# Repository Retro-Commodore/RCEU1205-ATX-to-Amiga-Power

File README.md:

# RCEU1205
 ATX to Amiga Power adapter for A500/600/1200 Tower
 
Make note that the pcb has not been testet yet, and shouldn't be considered a release just yet. 

# BOM

w/everything (*)
1x 24 pin ATX connector
5x Pins salvaged from a DIN connector
2x 4pin SIL header
7x 2pin SIL header

bare minimum (*)
1x 24 pin ATX connector
5x Pins salvaged from a DIN connector
1x 2pin SIL header

# Putting it all together
The pins from the DIN connector is soldered into the square din holes.

# Description
J2 is the power connector for the ATX power supply.

There are 2x 4pins headers for 12v psu's  pin1 = gnd, pin2 = 12v, pin3 = sense, pin4 = control
The 2x 2pins headers to the right gains access to pin 3 and 4 accordingly to the 12v pin header, in case you want to control the 12v fans using an arduino or similar.

There are 2x 2pins headers for 5v
And there are 2x 2pins headers for 3.3v
You can use these for whatever you want.

(*) the extra pin headers are not needed, but can be an extra help if you want to i.e. control fans using an arduino and temperature sensor.

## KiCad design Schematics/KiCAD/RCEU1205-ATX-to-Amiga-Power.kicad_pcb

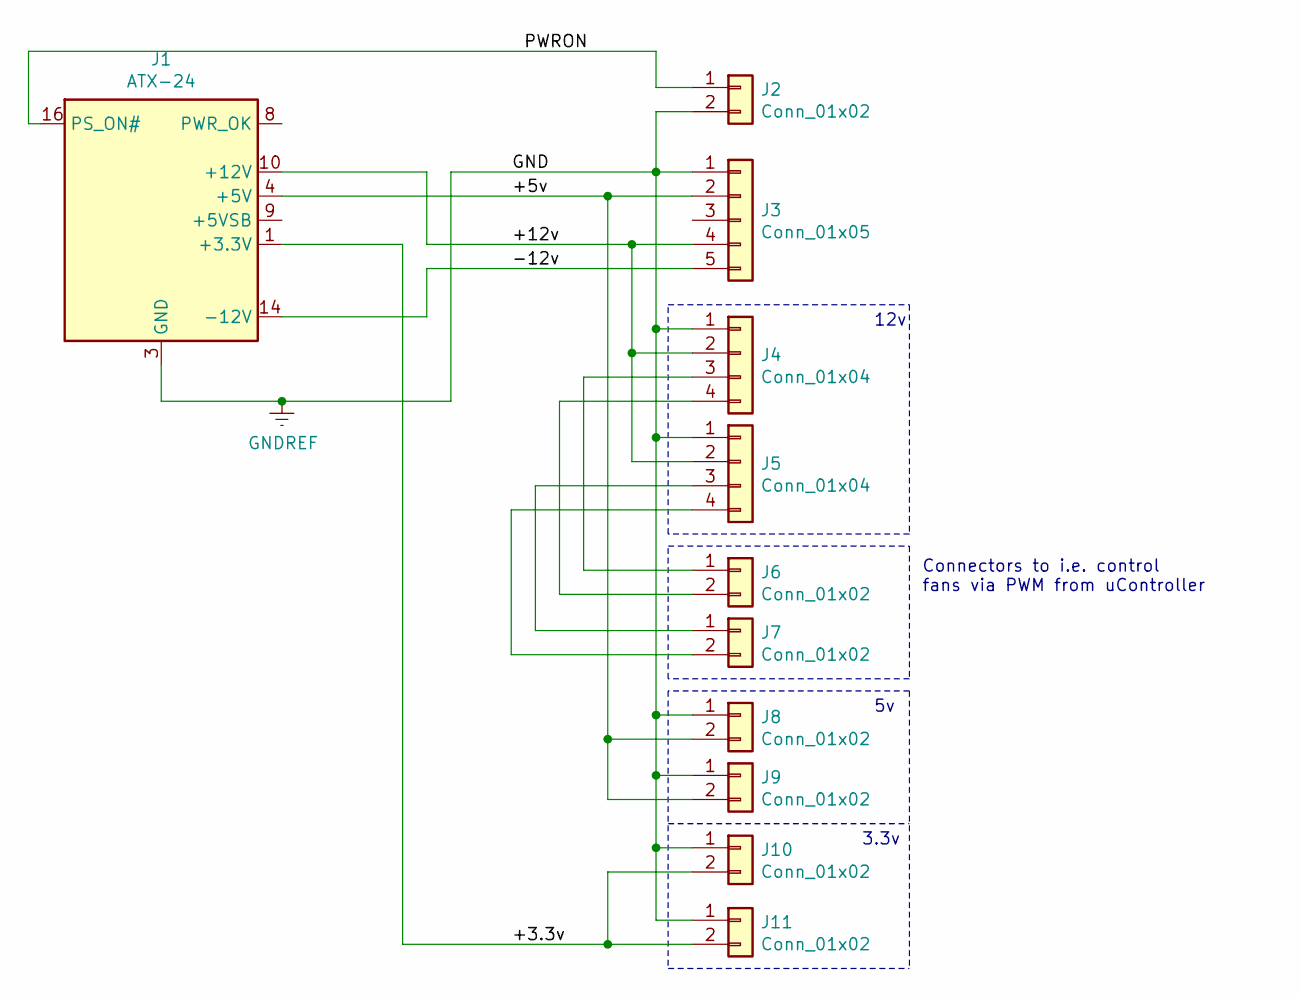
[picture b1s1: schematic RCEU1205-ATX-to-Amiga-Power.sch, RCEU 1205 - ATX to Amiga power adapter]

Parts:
J1: ATX-24; Molex_Mini-Fit_Jr_5566-24A_2x12_P4.20mm_Vertical
J2, J6, J7, J8, J9, J10, J11: Conn_01x02; PinHeader_1x02_P2.54mm_Vertical
J3: Conn_01x05; Connector_DIN_Square_5pin
J4, J5: Conn_01x04; PinHeader_1x04_P2.54mm_Vertical

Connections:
/+3.3v: J1.1 (+3.3V), J1.2 (+3.3V), J1.12 (+3.3V), J1.13 (+3.3V), J10.2, J11.2
/+5v: J1.4 (+5V), J1.6 (+5V), J1.21 (+5V), J1.22 (+5V), J1.23 (+5V), J3.2, J8.2, J9.2
/+12v: J1.10 (+12V), J1.11 (+12V), J3.4, J4.2, J5.2
/-12v: J1.14 (-12V), J3.5
/PWRON: J1.16 (PS_ON#), J2.1
GNDREF: J1.3 (GND), J1.5 (GND), J1.7 (GND), J1.15 (GND), J1.17 (GND), J1.18 (GND), J1.19 (GND), J1.24 (GND), J2.2, J3.1, J4.1, J5.1, J8.1, J9.1, J10.1, J11.1
unnamed: J4.3, J6.1
unnamed: J4.4, J6.2
unnamed: J5.3, J7.1
unnamed: J5.4, J7.2

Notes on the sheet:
3.3v
12v
Connectors to i.e. control fans via PWM from uController

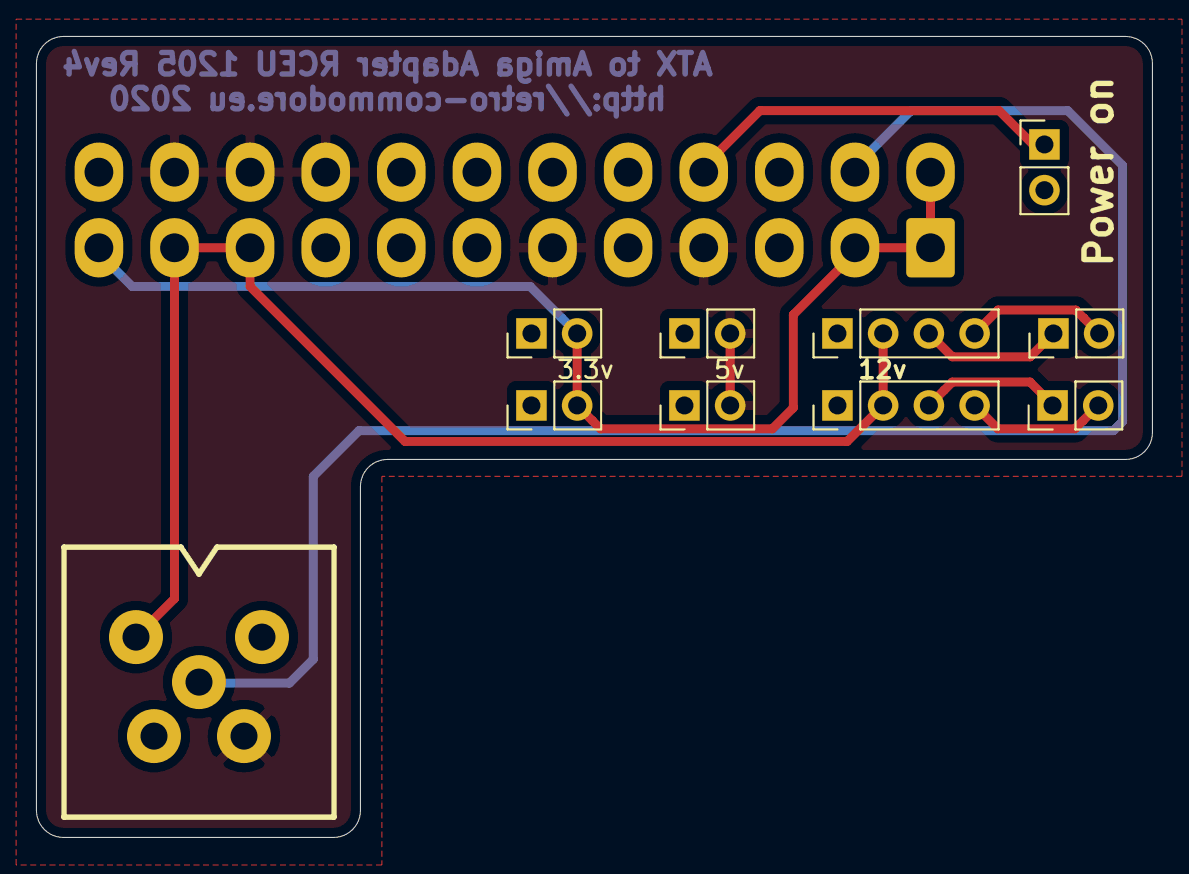
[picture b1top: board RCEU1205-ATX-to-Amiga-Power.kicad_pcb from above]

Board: 2 copper layers, 62.0 x 44.5 mm, 11 parts (0 on the bottom side), 10 nets.

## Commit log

2020-04-06 Create RCEU1205.jpg
    Added rendered pic
2020-08-23 Initial public release
2020-09-27 Fixing connector to be seated on the correct side + expanded holes for atx connector.
2020-09-27 Fixing som cosmetics
2020-11-25 Fixed ATX connector, rechecked pinout
2020-11-25 Bumped to rev4
2020-12-23 Moved gerber files to release tag
